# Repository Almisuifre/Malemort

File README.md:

# Malemort
Réseau de train Malemort

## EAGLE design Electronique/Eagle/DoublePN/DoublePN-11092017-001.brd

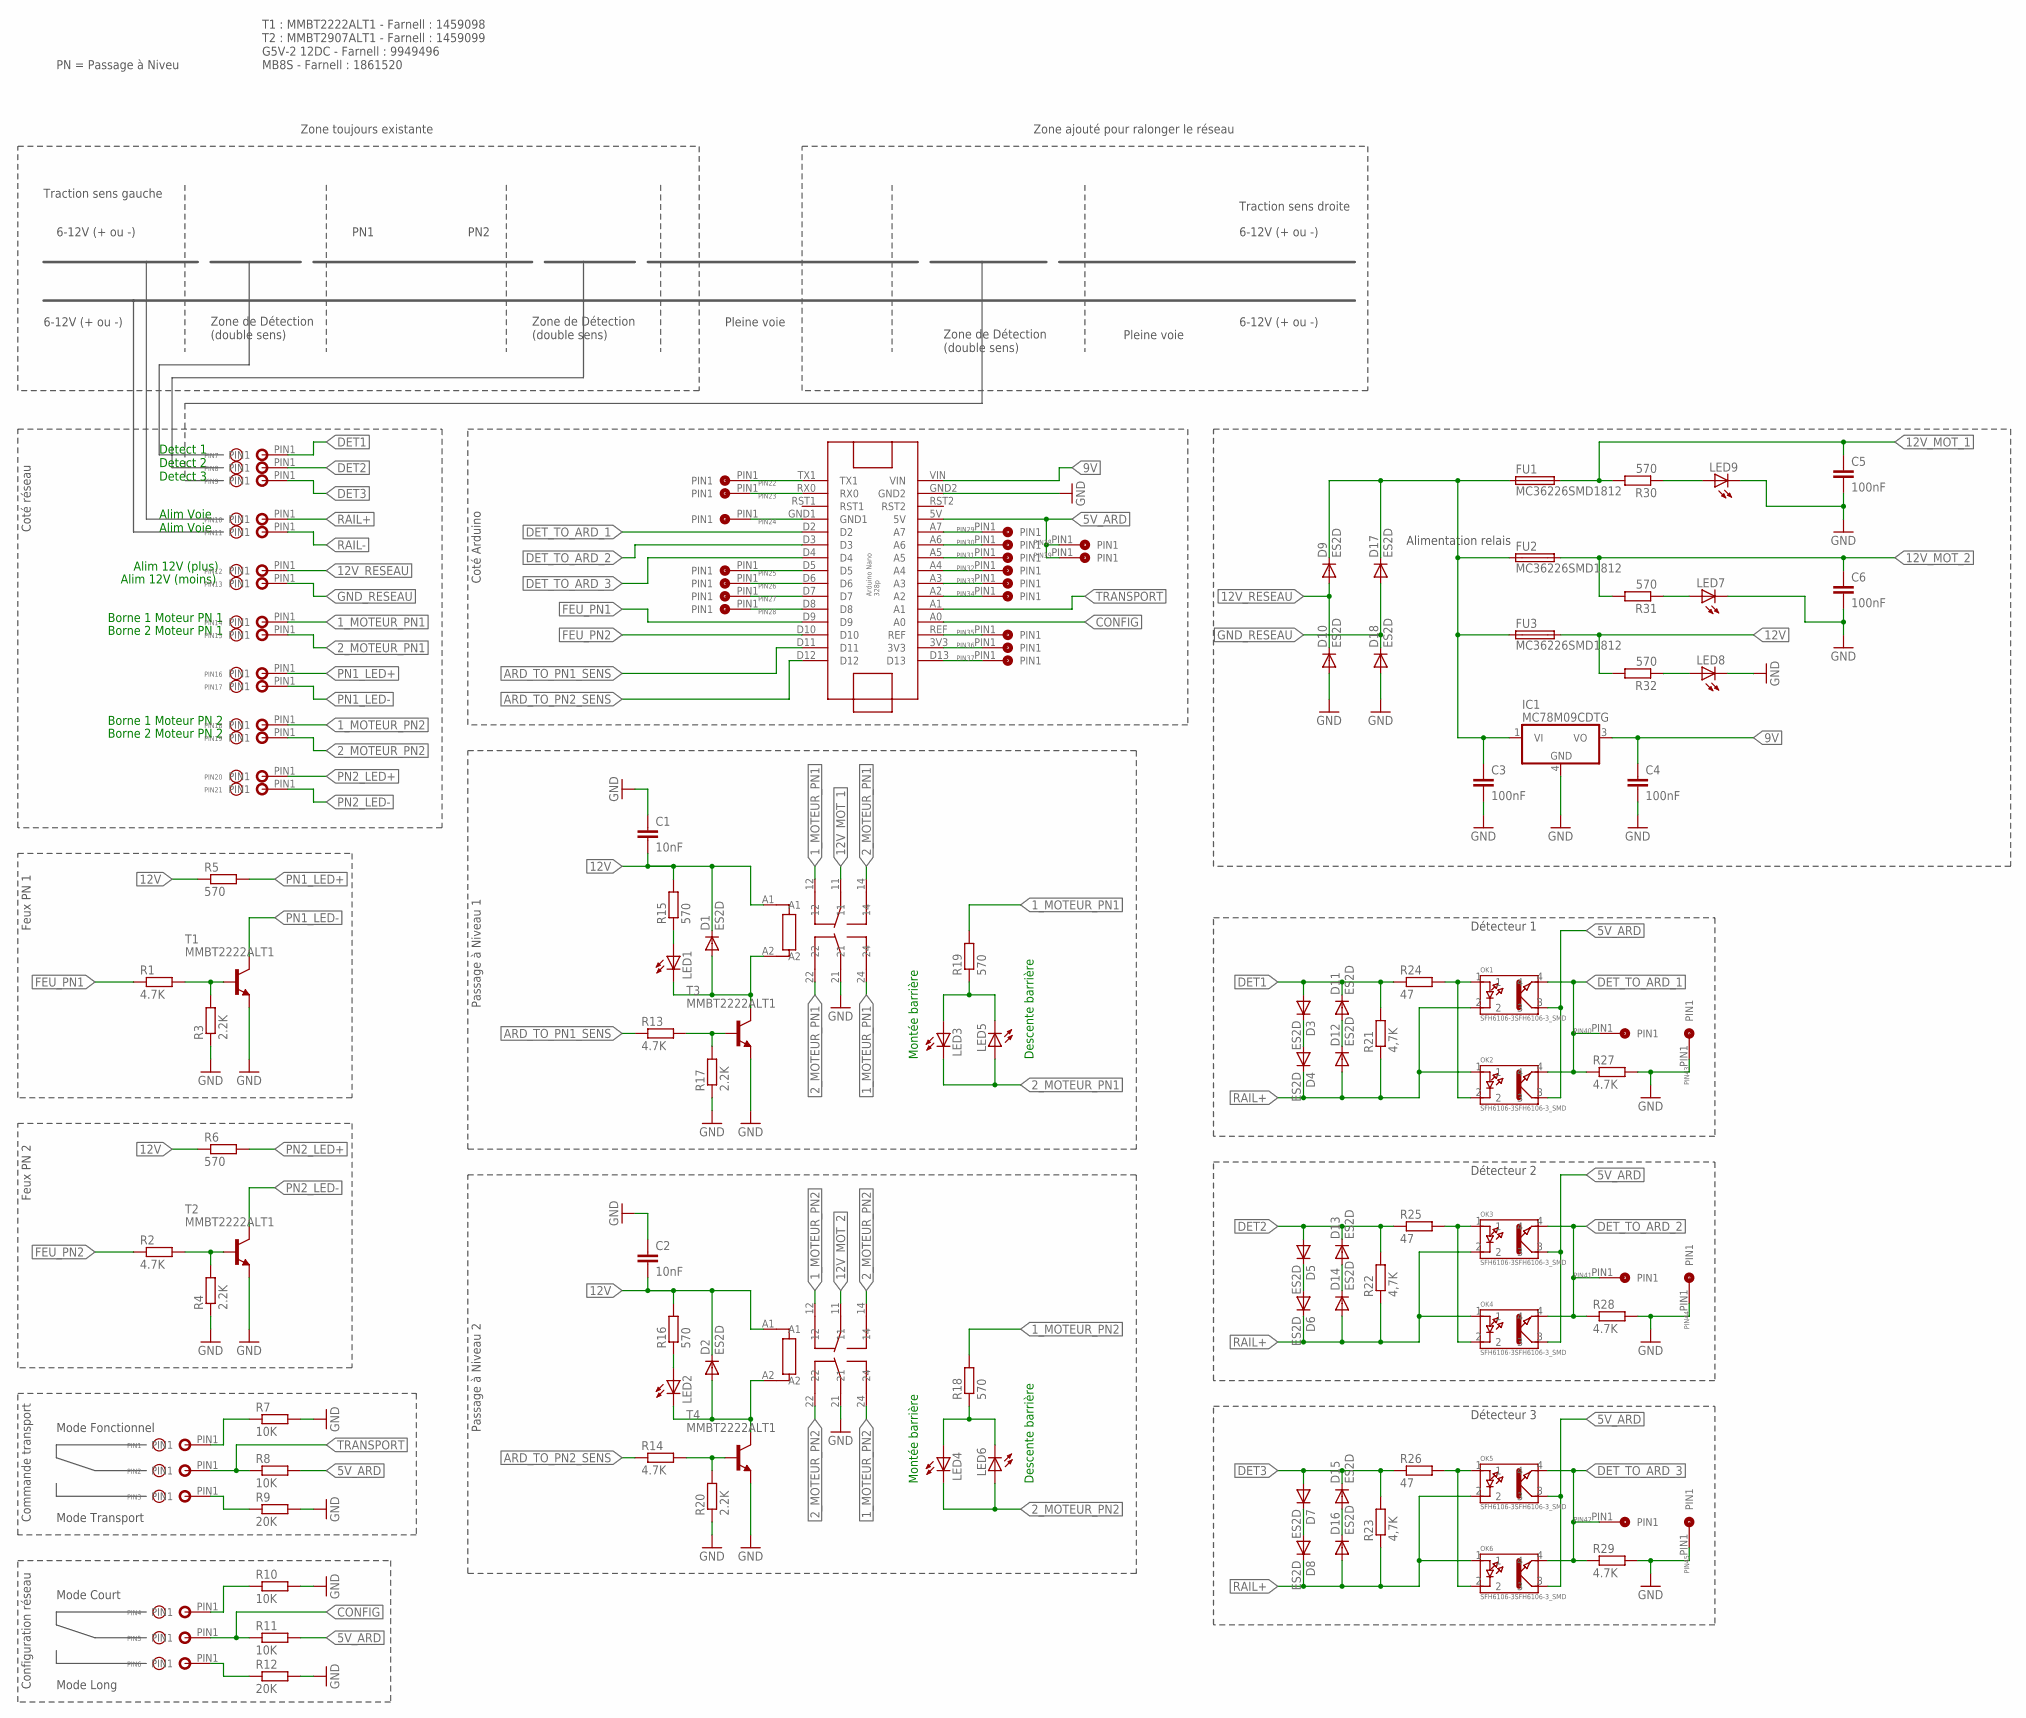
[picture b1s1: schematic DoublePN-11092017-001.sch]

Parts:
ARDUINO-NANO1: ARDUINO-NANO
C1, C2: 10nF; C0805
C3, C4, C5, C6: 100nF; C0805
D1, D2, D3, D4, D5, D6, D7, D8, D9, D10, D11, D12, D13, D14, D15, D16, D17, D18: ES2D; SMB
FU1, FU2, FU3: MC36226SMD1812; MC36226
IC1: MC78M09CDTG; DPACK_3
LED1, LED2, LED3, LED4, LED5, LED6, LED7, LED8, LED9: LEDCHIPLED_0805; CHIPLED_0805
OK1, OK2, OK3, OK4, OK5, OK6: SFH6106-3SFH6106-3_SMD; SFH6106-3
PIN1, PIN2, PIN3, PIN4, PIN5, PIN6, PIN7, PIN8, PIN9, PIN10, PIN11, PIN12, PIN13, PIN14, PIN15, PIN16, PIN17, PIN18, PIN19, PIN20, PIN21: CON-FILTRAVERSANT-1FILTRAVERSANT-1; CON-FILTRAVERSANT-1
PIN22, PIN23, PIN24, PIN25, PIN26, PIN27, PIN28, PIN29, PIN30, PIN31, PIN32, PIN33, PIN34, PIN35, PIN36, PIN37, PIN38, PIN39, PIN40, PIN41, PIN42, PIN43, PIN44, PIN45: CON-TRAV-1PIN; CON-TRAV-1
R1, R2, R13, R14, R27, R28, R29: 4.7K; R0805
R3, R4, R17, R20: 2.2K; R0805
R5, R6, R15, R16, R18, R19, R30, R31, R32: 570; R0805
R7, R8, R10, R11: 10K; R0805
R9, R12: 20K; R0805
R21, R22, R23: 4,7K; R0805
R24, R25, R26: 47; R0805
RLS1, RLS2: FINDER-DPDT-12VFINDER-DPDT-12V; FINDER-DPDT-12V
T1, T2, T3, T4: MMBT2222ALT1; SOT23-BEC

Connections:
1_MOTEUR_PN1: PIN14.PIN1, R19.2, RLS1.12, RLS1.24
1_MOTEUR_PN2: PIN18.PIN1, R18.2, RLS2.12, RLS2.24
2_MOTEUR_PN1: LED3.C, LED5.A, PIN15.PIN1, RLS1.14, RLS1.22
2_MOTEUR_PN2: LED4.C, LED6.A, PIN19.PIN1, RLS2.14, RLS2.22
5V_ARD: ARDUINO-NANO1.5V, OK1.3, OK2.3, OK3.3, OK4.3, OK5.3, OK6.3, PIN38.PIN1, PIN39.PIN1, R8.2, R11.2
9V: ARDUINO-NANO1.VIN, C4.1, IC1.3 (VO)
12V: C1.2, C2.2, D1.C, D2.C, FU3.2, R5.1, R6.1, R15.2, R16.2, R32.2, RLS1.A1, RLS2.A1
12V_MOT_1: C5.1, FU1.2, R30.2, RLS1.11
12V_MOT_2: C6.1, FU2.2, R31.2, RLS2.11
12V_RESEAU: D9.A, D10.C, PIN12.PIN1
ARD_TO_PN1_SENS: ARDUINO-NANO1.D11, R13.1
ARD_TO_PN2_SENS: ARDUINO-NANO1.D12, R14.1
CONFIG: ARDUINO-NANO1.A0, PIN5.PIN1, R11.1
DET1: D3.A, D11.C, PIN7.PIN1, R21.2, R24.1
DET2: D5.A, D13.C, PIN8.PIN1, R22.2, R25.1
DET3: D7.A, D15.C, PIN9.PIN1, R23.2, R26.1
DET_TO_ARD_1: ARDUINO-NANO1.D2, OK1.4, OK2.4, PIN40.PIN1, R27.1
DET_TO_ARD_2: ARDUINO-NANO1.D3, OK3.4, OK4.4, PIN41.PIN1, R28.1
DET_TO_ARD_3: ARDUINO-NANO1.D4, OK5.4, OK6.4, PIN42.PIN1, R29.1
FEU_PN1: ARDUINO-NANO1.D9, R1.1
FEU_PN2: ARDUINO-NANO1.D10, R2.1
GND: ARDUINO-NANO1.GND2, C1.1, C2.1, C3.2, C4.2, C5.2, C6.2, D10.A, D18.A, IC1.4 (GND), LED7.C, LED8.C, LED9.C, PIN43.PIN1, PIN44.PIN1, PIN45.PIN1, R3.1, R4.1, R7.2, R9.2, R10.2, R12.2, R17.1, R20.1, R27.2, R28.2, R29.2, RLS1.21, RLS2.21, T1.E, T2.E, T3.E, T4.E
GND_RESEAU: D17.A, D18.C, PIN13.PIN1
unnamed: OK1.1, OK2.2, R24.2
unnamed: D3.C, D4.A
unnamed: D11.A, D12.C
unnamed: LED3.A, LED5.C, R19.1
unnamed: R13.2, R17.2, T3.B
unnamed: D5.C, D6.A
unnamed: D1.A, LED1.C, RLS1.A2, T3.C
unnamed: D13.A, D14.C
unnamed: LED1.A, R15.1
unnamed: OK3.1, OK4.2, R25.2
unnamed: D7.C, D8.A
unnamed: D15.A, D16.C
unnamed: OK5.1, OK6.2, R26.2
unnamed: D2.A, LED2.C, RLS2.A2, T4.C
unnamed: LED9.A, R30.1
unnamed: LED4.A, LED6.C, R18.1
unnamed: R14.2, R20.2, T4.B
unnamed: LED2.A, R16.1
unnamed: ARDUINO-NANO1.GND1, PIN24.PIN1
unnamed: R2.2, R4.2, T2.B
unnamed: ARDUINO-NANO1.D7, PIN27.PIN1
unnamed: R1.2, R3.2, T1.B
unnamed: ARDUINO-NANO1.D8, PIN28.PIN1
unnamed: LED7.A, R31.1
unnamed: ARDUINO-NANO1.A7, PIN29.PIN1
unnamed: ARDUINO-NANO1.A6, PIN30.PIN1
unnamed: ARDUINO-NANO1.A5, PIN31.PIN1
unnamed: ARDUINO-NANO1.A4, PIN32.PIN1
unnamed: ARDUINO-NANO1.A3, PIN33.PIN1
unnamed: ARDUINO-NANO1.A2, PIN34.PIN1
unnamed: ARDUINO-NANO1.D6, PIN26.PIN1
unnamed: ARDUINO-NANO1.D5, PIN25.PIN1
unnamed: ARDUINO-NANO1.RX0, PIN23.PIN1
unnamed: ARDUINO-NANO1.TX1, PIN22.PIN1
unnamed: PIN4.PIN1, R10.1
unnamed: PIN1.PIN1, R7.1
unnamed: ARDUINO-NANO1.REF, PIN35.PIN1
unnamed: ARDUINO-NANO1.3V3, PIN36.PIN1
unnamed: ARDUINO-NANO1.D13, PIN37.PIN1
unnamed: PIN6.PIN1, R12.1
unnamed: PIN3.PIN1, R9.1
unnamed: C3.1, D9.C, D17.C, FU1.1, FU2.1, FU3.1, IC1.1 (VI)
unnamed: LED8.A, R32.1
PN1_LED+: PIN16.PIN1, R5.2
PN1_LED-: PIN17.PIN1, T1.C
PN2_LED+: PIN20.PIN1, R6.2
PN2_LED-: PIN21.PIN1, T2.C
RAIL+: D4.C, D6.C, D8.C, D12.A, D14.A, D16.A, OK1.2, OK2.1, OK3.2, OK4.1, OK5.2, OK6.1, PIN10.PIN1, R21.1, R22.1, R23.1
RAIL-: PIN11.PIN1
TRANSPORT: ARDUINO-NANO1.A1, PIN2.PIN1, R8.1

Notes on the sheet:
Alim Voie Alim Voie
Detect 1 Detect 2 Detect 3
Traction sens gauche
6-12V (+ ou -)
Traction sens droite
Zone toujours existante
Zone ajouté pour ralonger le réseau
PN2
PN1
PN = Passage à Niveu
Zone de Détection (double sens)
Pleine voie
Coté réseau
Coté Arduino
Détecteur 1
T1 : MMBT2222ALT1 - Farnell : 1459098 T2 : MMBT2907ALT1 - Farnell : 1459099 G5V-2 12DC - Farnell : 9949496 MB8S - Farnell : 1861520
Alim 12V (plus)
Alim 12V (moins)
Alimentation relais
Borne 1 Moteur PN 1
Borne 2 Moteur PN 1
Borne 2 Moteur PN 2
Borne 1 Moteur PN 2
Montée barrière
Descente barrière
Passage à Niveau 1
Feux PN 1
Mode Court
Mode Long
Configuration réseau
Mode Fonctionnel
Mode Transport
Commande transport
Détecteur 2
Détecteur 3
Feux PN 2
Passage à Niveau 2

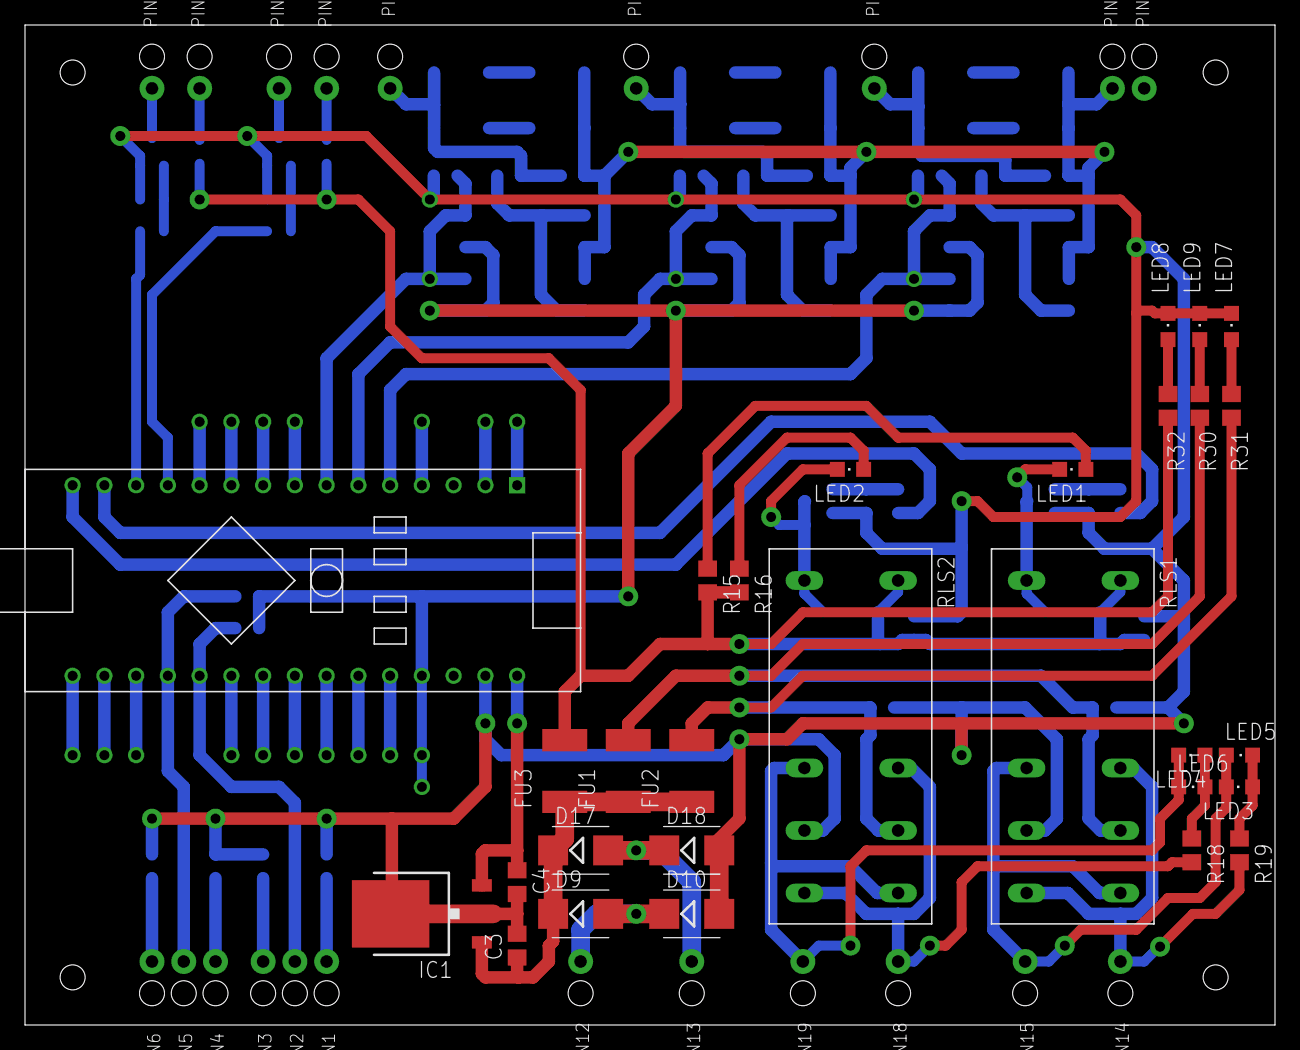
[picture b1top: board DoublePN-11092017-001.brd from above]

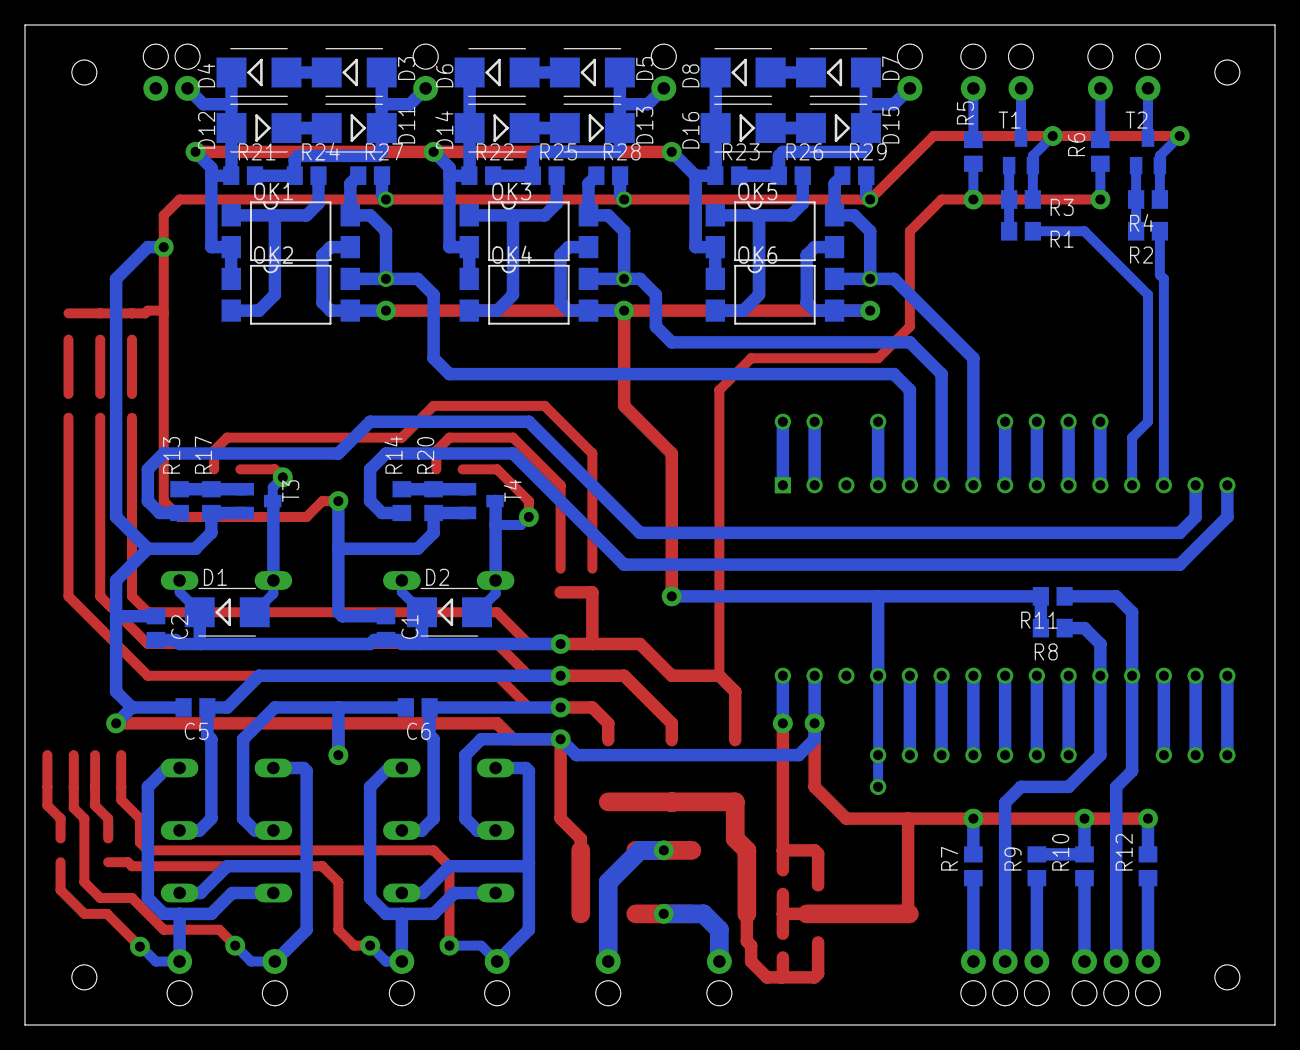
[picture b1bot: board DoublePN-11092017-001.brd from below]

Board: 2 copper layers, 100.0 x 80.0 mm, 127 parts (54 on the bottom side), 72 nets.

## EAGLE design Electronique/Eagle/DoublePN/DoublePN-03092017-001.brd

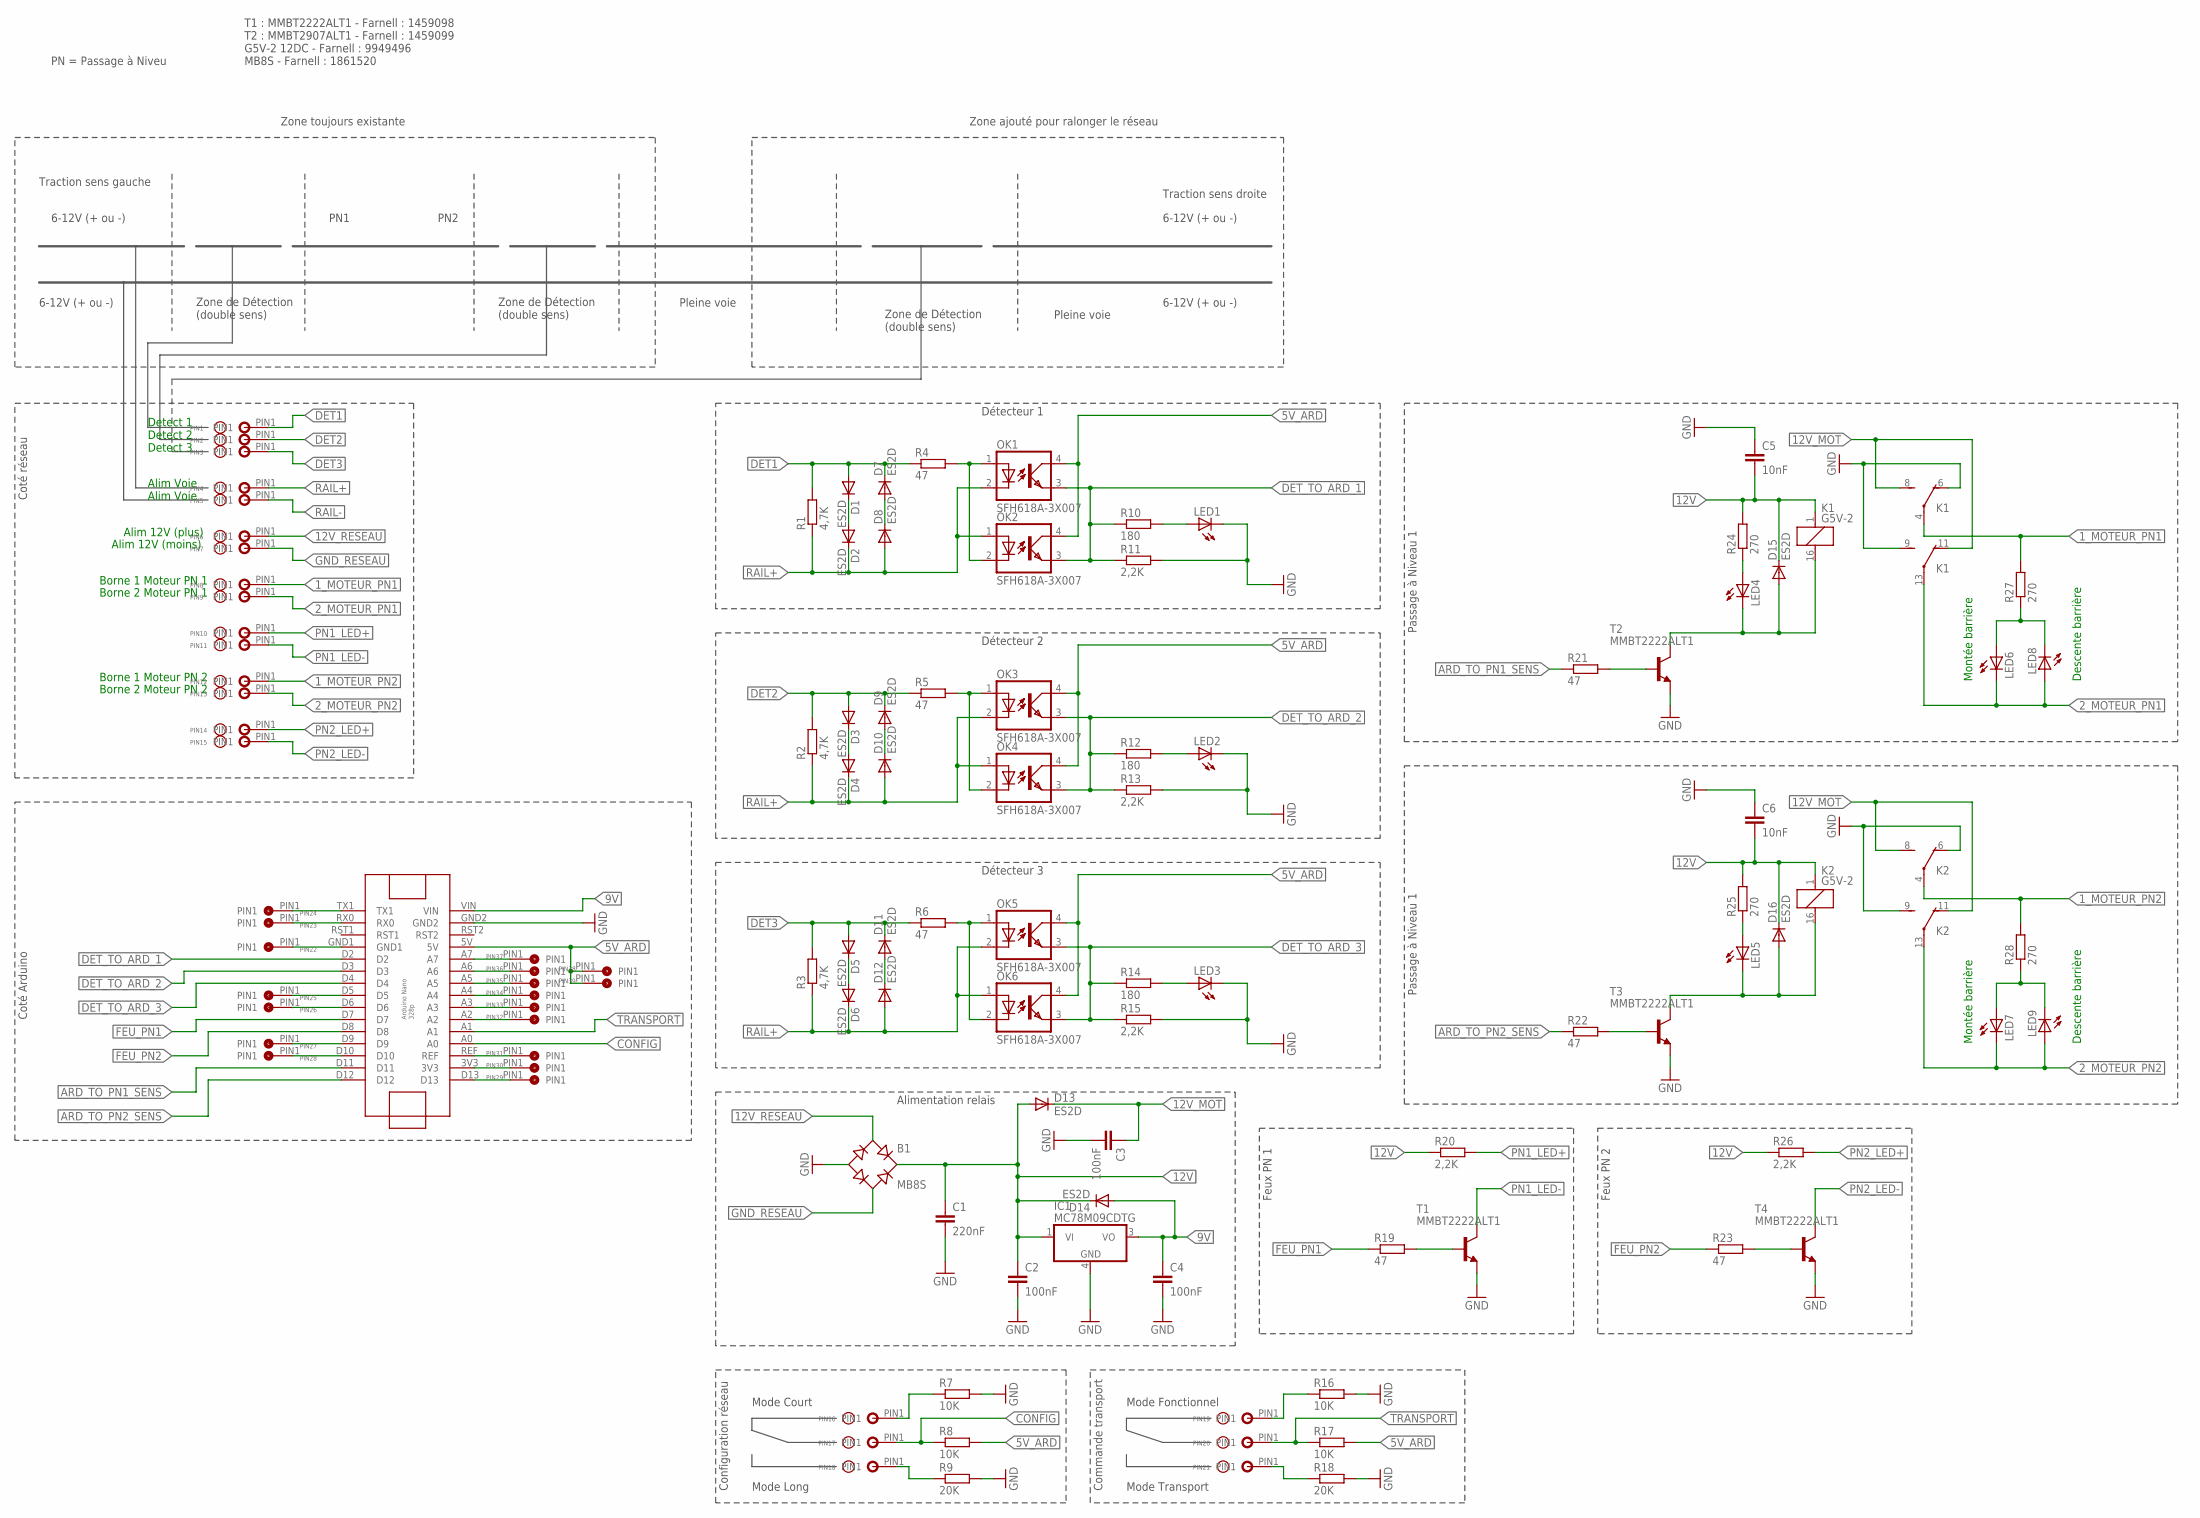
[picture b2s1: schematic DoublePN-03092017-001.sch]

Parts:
ARDUINO-NANO1: ARDUINO-NANO
B1: MB8S; SOIC-4
C1: 220nF; C0805
C2, C3, C4: 100nF; C0805
C5, C6: 10nF; C0805
D1, D2, D3, D4, D5, D6, D7, D8, D9, D10, D11, D12, D13, D14, D15, D16: ES2D; SMB
IC1: MC78M09CDTG; DPACK_3
K1, K2: G5V-2
LED1, LED2, LED3, LED4, LED5, LED6, LED7, LED8, LED9: LEDCHIPLED_0805; CHIPLED_0805
OK1, OK2, OK3, OK4, OK5, OK6: SFH618A-3X007; SMD4-7
PIN1, PIN2, PIN3, PIN4, PIN5, PIN6, PIN7, PIN8, PIN9, PIN10, PIN11, PIN12, PIN13, PIN14, PIN15, PIN16, PIN17, PIN18, PIN19, PIN20, PIN21: CON-FILTRAVERSANT-1FILTRAVERSANT-1; CON-FILTRAVERSANT-1
PIN22, PIN23, PIN24, PIN25, PIN26, PIN27, PIN28, PIN29, PIN30, PIN31, PIN32, PIN33, PIN34, PIN35, PIN36, PIN37, PIN38, PIN39: CON-TRAV-1PIN; CON-TRAV-1
R1, R2, R3: 4,7K; R0805
R4, R5, R6, R19, R21, R22, R23: 47; R0805
R7, R8, R16, R17: 10K; R0805
R9, R18: 20K; R0805
R10, R12, R14: 180; R0805
R11, R13, R15, R20, R26: 2,2K; R0805
R24, R25, R27, R28: 270; R0805
T1, T2, T3, T4: MMBT2222ALT1; SOT23-BEC

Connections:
1_MOTEUR_PN1: K1.4, PIN8.PIN1, R27.2
1_MOTEUR_PN2: K2.4, PIN12.PIN1, R28.2
2_MOTEUR_PN1: K1.13, LED6.C, LED8.A, PIN9.PIN1
2_MOTEUR_PN2: K2.13, LED7.C, LED9.A, PIN13.PIN1
5V_ARD: ARDUINO-NANO1.5V, OK1.4 (COL), OK2.4 (COL), OK3.4 (COL), OK4.4 (COL), OK5.4 (COL), OK6.4 (COL), PIN38.PIN1, PIN39.PIN1, R8.2, R17.2
9V: ARDUINO-NANO1.VIN, C4.1, D14.A, IC1.3 (VO)
12V: B1.+, C1.1, C2.1, C5.2, C6.2, D13.A, D14.C, D15.C, D16.C, IC1.1 (VI), K1.1, K2.1, R20.1, R24.2, R25.2, R26.1
12V_MOT: C3.1, D13.C, K1.8 (S), K1.11 (O), K2.8 (S), K2.11 (O)
12V_RESEAU: B1.~1 (AC1), PIN6.PIN1
ARD_TO_PN1_SENS: ARDUINO-NANO1.D11, R21.1
ARD_TO_PN2_SENS: ARDUINO-NANO1.D12, R22.1
CONFIG: ARDUINO-NANO1.A0, PIN17.PIN1, R8.1
DET1: D1.A, D7.C, PIN1.PIN1, R1.2, R4.1
DET2: D3.A, D9.C, PIN2.PIN1, R2.2, R5.1
DET3: D5.A, D11.C, PIN3.PIN1, R3.2, R6.1
DET_TO_ARD_1: ARDUINO-NANO1.D2, OK1.3 (EMIT), OK2.3 (EMIT), R10.1, R11.1
DET_TO_ARD_2: ARDUINO-NANO1.D3, OK3.3 (EMIT), OK4.3 (EMIT), R12.1, R13.1
DET_TO_ARD_3: ARDUINO-NANO1.D4, OK5.3 (EMIT), OK6.3 (EMIT), R14.1, R15.1
FEU_PN1: ARDUINO-NANO1.D7, R19.1
FEU_PN2: ARDUINO-NANO1.D8, R23.1
GND: ARDUINO-NANO1.GND2, B1.-, C1.2, C2.2, C3.2, C4.2, C5.1, C6.1, IC1.4 (GND), K1.6 (O), K1.9 (S), K2.6 (O), K2.9 (S), LED1.C, LED2.C, LED3.C, R7.2, R9.2, R11.2, R13.2, R15.2, R16.2, R18.2, T1.E, T2.E, T3.E, T4.E
GND_RESEAU: B1.~2 (AC2), PIN7.PIN1
unnamed: OK1.1 (A), OK2.2 (C), R4.2
unnamed: D1.C, D2.A
unnamed: D7.A, D8.C
unnamed: LED6.A, LED8.C, R27.1
unnamed: R21.2, T2.B
unnamed: LED1.A, R10.2
unnamed: D15.A, K1.16 (2), LED4.C, T2.C
unnamed: D3.C, D4.A
unnamed: LED4.A, R24.1
unnamed: D9.A, D10.C
unnamed: OK3.1 (A), OK4.2 (C), R5.2
unnamed: LED2.A, R12.2
unnamed: D5.C, D6.A
unnamed: D11.A, D12.C
unnamed: OK5.1 (A), OK6.2 (C), R6.2
unnamed: LED3.A, R14.2
unnamed: LED5.A, R25.1
unnamed: D16.A, K2.16 (2), LED5.C, T3.C
unnamed: ARDUINO-NANO1.GND1, PIN22.PIN1
unnamed: LED7.A, LED9.C, R28.1
unnamed: R23.2, T4.B
unnamed: R19.2, T1.B
unnamed: R22.2, T3.B
unnamed: ARDUINO-NANO1.A7, PIN37.PIN1
unnamed: ARDUINO-NANO1.A6, PIN36.PIN1
unnamed: ARDUINO-NANO1.A5, PIN35.PIN1
unnamed: ARDUINO-NANO1.A4, PIN34.PIN1
unnamed: ARDUINO-NANO1.A3, PIN33.PIN1
unnamed: ARDUINO-NANO1.A2, PIN32.PIN1
unnamed: ARDUINO-NANO1.D10, PIN28.PIN1
unnamed: ARDUINO-NANO1.D9, PIN27.PIN1
unnamed: ARDUINO-NANO1.D6, PIN26.PIN1
unnamed: ARDUINO-NANO1.D5, PIN25.PIN1
unnamed: ARDUINO-NANO1.RX0, PIN23.PIN1
unnamed: ARDUINO-NANO1.TX1, PIN24.PIN1
unnamed: PIN16.PIN1, R7.1
unnamed: PIN19.PIN1, R16.1
unnamed: ARDUINO-NANO1.REF, PIN31.PIN1
unnamed: ARDUINO-NANO1.3V3, PIN30.PIN1
unnamed: ARDUINO-NANO1.D13, PIN29.PIN1
unnamed: PIN18.PIN1, R9.1
unnamed: PIN21.PIN1, R18.1
PN1_LED+: PIN10.PIN1, R20.2
PN1_LED-: PIN11.PIN1, T1.C
PN2_LED+: PIN14.PIN1, R26.2
PN2_LED-: PIN15.PIN1, T4.C
RAIL+: D2.C, D4.C, D6.C, D8.A, D10.A, D12.A, OK1.2 (C), OK2.1 (A), OK3.2 (C), OK4.1 (A), OK5.2 (C), OK6.1 (A), PIN4.PIN1, R1.1, R2.1, R3.1
RAIL-: PIN5.PIN1
TRANSPORT: ARDUINO-NANO1.A1, PIN20.PIN1, R17.1

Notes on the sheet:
Alim Voie Alim Voie
Detect 1 Detect 2 Detect 3
Traction sens gauche
6-12V (+ ou -)
Traction sens droite
Zone toujours existante
Zone ajouté pour ralonger le réseau
PN2
PN1
PN = Passage à Niveu
Zone de Détection (double sens)
Pleine voie
Coté réseau
Coté Arduino
Détecteur 1
T1 : MMBT2222ALT1 - Farnell : 1459098 T2 : MMBT2907ALT1 - Farnell : 1459099 G5V-2 12DC - Farnell : 9949496 MB8S - Farnell : 1861520
Alim 12V (plus)
Alim 12V (moins)
Alimentation relais
Borne 1 Moteur PN 1
Borne 2 Moteur PN 1
Borne 2 Moteur PN 2
Borne 1 Moteur PN 2
Montée barrière
Descente barrière
Passage à Niveau 1
Détecteur 2
Détecteur 3
Feux PN 1
Feux PN 2
Mode Court
Mode Long
Configuration réseau
Mode Fonctionnel
Mode Transport
Commande transport

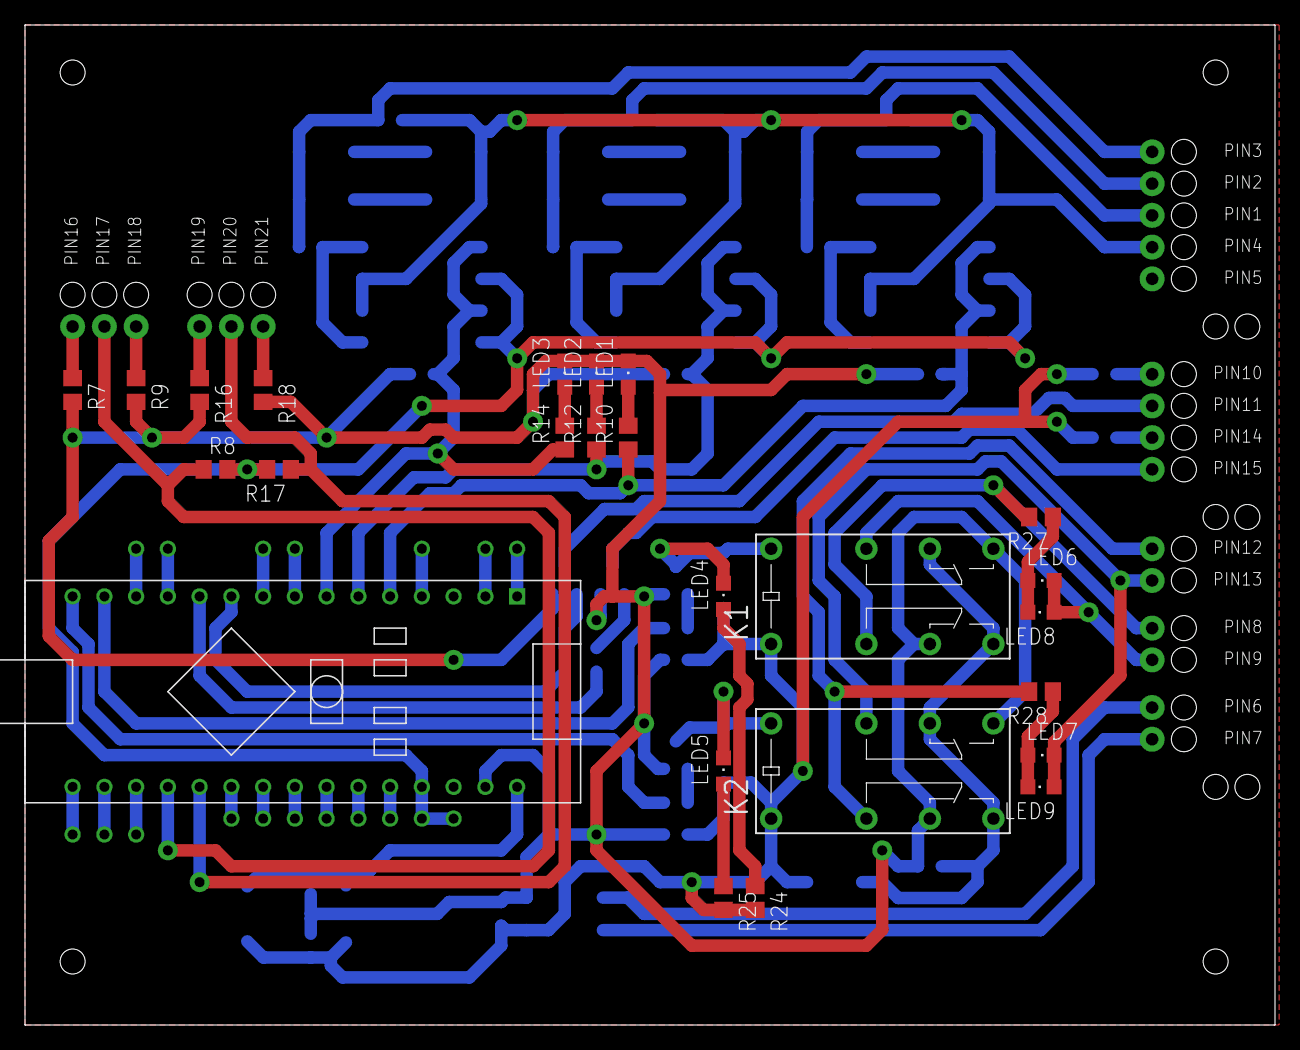
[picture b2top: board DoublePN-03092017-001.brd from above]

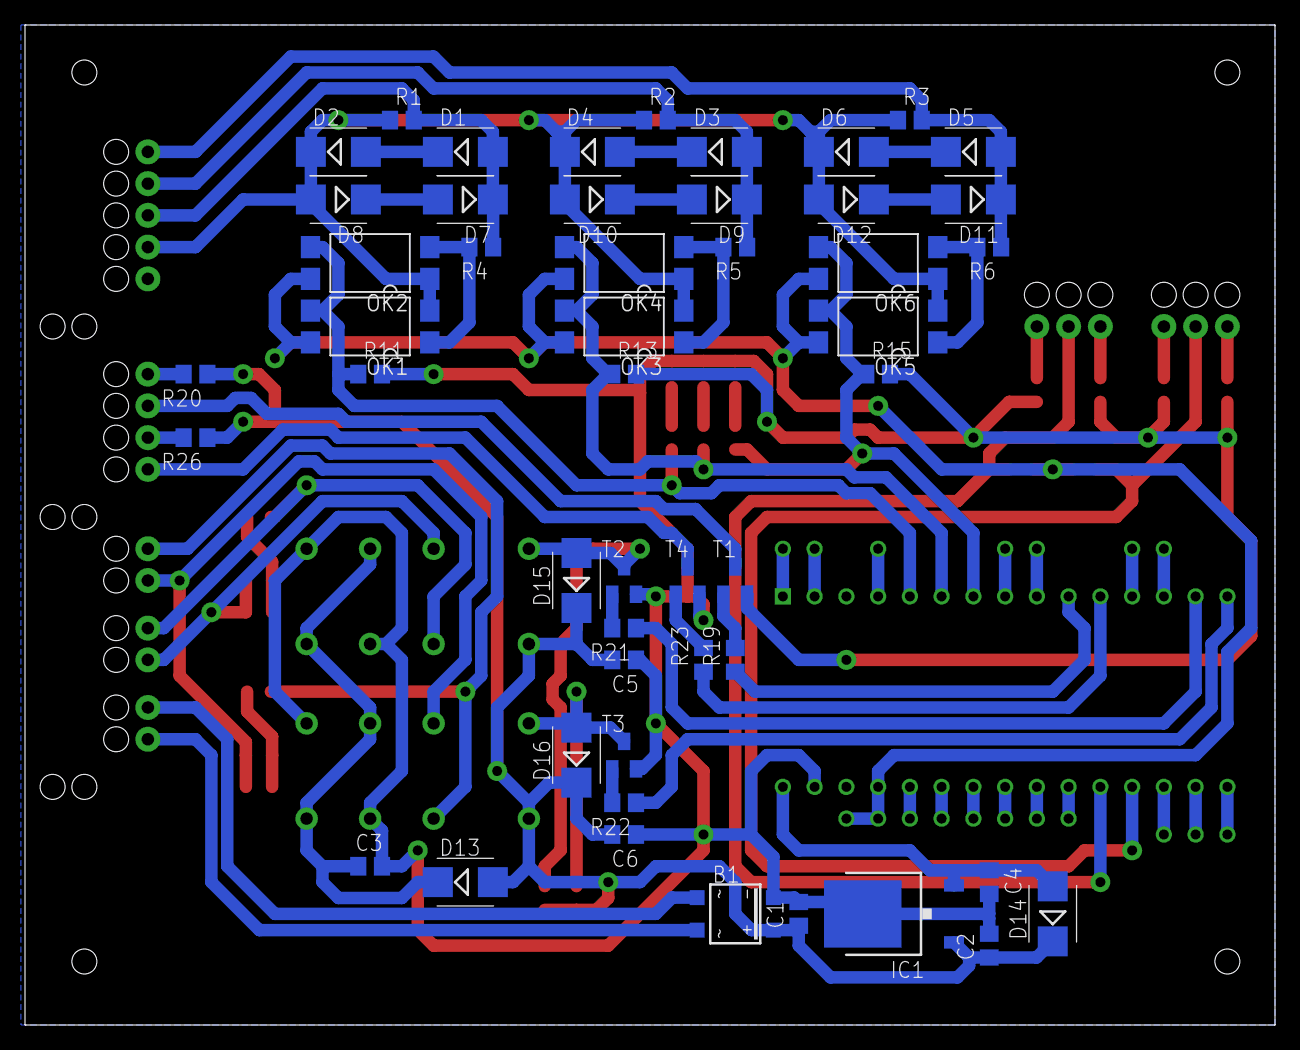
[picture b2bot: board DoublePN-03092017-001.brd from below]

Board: 2 copper layers, 100.0 x 80.0 mm, 113 parts (49 on the bottom side), 70 nets.

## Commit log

2016-12-11 Add files via upload
    Version 0 à tester in situ
2016-12-11 Add files via upload
    Ajout de la librairie FlexiTimer2
2017-01-22 Création dela nouvelle version réseau Malemort
    Création de la nouvelle version soft du réseau de train Malemort
2017-02-05 Nouvelle version
    Cette version fonctionne
    - Ajout écran LCD
    - Révision temporisations
2017-02-18 Mise à jour tempos
    Mise à jour tempos
2017-09-09 Create new sketch automatic independant
    Création d'un nouveau programme pour arduino nano. Gestion d'un double Pn disponible sur le réseau Malemort.
2017-09-10 Create new rep. Electronique and Eagle
    Création d'un répertoire nommé Electronique. A l'intérieur, se trouve les fichiers Eagle du montage.
2017-09-11 Remove electronic bad
    Remove electronic bad
2017-09-11 New Electronic Base
    New Electronic Base
2017-09-15 Nouvelle version
    Pour la nouvelle carte. Nouvelle version soft !
2017-09-15 Mise à jour carte
    Mise à jour carte
2017-09-17 Add chronogram
    Ajout des chronogrammes
2017-09-17 Add dia chronogram
    Ajout des cronogrammes utilisable avec le logiciel DIA
2018-04-17 Schéma
    Mise à jour du schéma DB25 raccordement réseau
